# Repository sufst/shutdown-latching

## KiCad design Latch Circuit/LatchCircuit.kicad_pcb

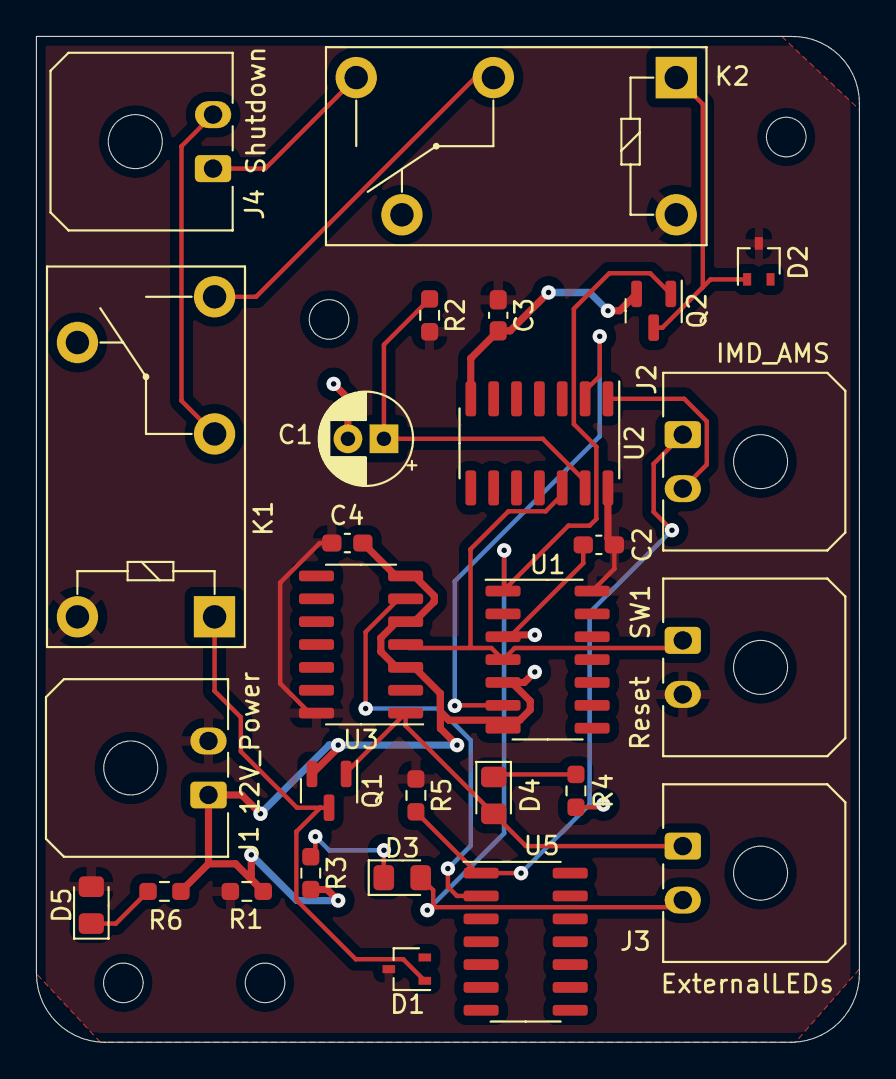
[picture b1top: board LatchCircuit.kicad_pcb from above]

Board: 2 copper layers, 45.7 x 55.9 mm, 32 parts (0 on the bottom side), 18 nets.

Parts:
C1: 10u; CP_Radial_D5.0mm_P2.00mm
C2, C3, C4: 100n; C_0603_1608Metric_Pad1.08x0.95mm_HandSolder
D1, D2: BAT54W; SOT-323_SC-70
D3, D4, D5: LED; LED_0805_2012Metric_Pad1.15x1.40mm_HandSolder
H1, H2, H3, H4: MountingHole; MountingHole_2.2mm_M2
J1: 12V_Power; Molex_Micro-Fit_3.0_43650-0200_1x02_P3.00mm_Horizontal
J2: IMD_AMS; Molex_Micro-Fit_3.0_43650-0200_1x02_P3.00mm_Horizontal
J3: ExternalLEDs; Molex_Micro-Fit_3.0_43650-0200_1x02_P3.00mm_Horizontal
J4: Shutdown; Molex_Micro-Fit_3.0_43650-0200_1x02_P3.00mm_Horizontal
K1, K2: G5Q-1EU DC12; Relay_SPDT_Omron-G5Q-1
Q1, Q2: XP262N7002TR-G; SOT-23
R1, R2, R5: 10k; R_0603_1608Metric_Pad0.98x0.95mm_HandSolder
R3, R4, R6: 1k; R_0603_1608Metric_Pad0.98x0.95mm_HandSolder
SW1: Reset; Molex_Micro-Fit_3.0_43650-0200_1x02_P3.00mm_Horizontal
U1, U3: 4013; SOIC-14_3.9x8.7mm_P1.27mm
U2, U5: 40106; SOIC-14_3.9x8.7mm_P1.27mm

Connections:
+12V: C2.1, C3.1, C4.1, D1.3 (K), D2.3 (K), D5.2 (A), J1.2, K1.5, K2.5, R1.1, R2.2, R5.1, SW1.2, U1.14 (VDD), U2.14 (VDD), U3.14 (VDD)
/AMS_FAULT_LATCHED: D4.2 (A), J3.1, Q1.1 (G), U3.1 (Q)
/IMD_FAULT_LATCHED: D3.2 (A), J3.2, Q2.1 (G), U1.1 (Q)
/IMD_OK_{HS}: J2.2, U2.1
/POR: SW1.1, U1.4 (R), U2.12, U3.4 (R)
/SHUTDOWN_IN: J4.1, K2.3
/SHUTDOWN_OUT: J4.2, K1.2
/~AMS_NO_FAULT: J2.1, R5.2, U5.1
GND: C1.2, C2.2, C3.2, C4.2, J1.1, Q1.2 (S), Q2.2 (S), R1.2, R3.2, R4.2, R6.2, U1.3 (C), U1.5 (D), U1.7 (VSS), U2.7 (VSS), U3.3 (C), U3.5 (D), U3.7 (VSS)
unnamed: C1.1, R2.1, U2.13
unnamed: D1.1 (A), K1.1, Q1.3 (D)
unnamed: D2.1 (A), K2.1, Q2.3 (D)
unnamed: D3.1 (K), R3.1
unnamed: D4.1 (K), R4.1
unnamed: D5.1 (K), R6.1
unnamed: K1.3, K2.2
unnamed: U1.6 (S), U2.2
unnamed: U3.6 (S), U5.2

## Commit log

2022-03-09 Added Latch Circuit files
2022-03-15 update circuitry to include relays; change from screw terminals to connectors
2022-03-16 add gitignore
2022-03-16 separate latching to sheet; create windowing sheet; minor cleanup/refactoring
2022-03-16 update gitignore
2022-03-16 (wip) update OK condition inputs from IMD, AMS
2022-03-28 update schematic (ESF v1 submission)
2022-04-10 update schematic
2022-04-10 remove superfluous relay
2022-05-15 update schematic; add WIP pcb
